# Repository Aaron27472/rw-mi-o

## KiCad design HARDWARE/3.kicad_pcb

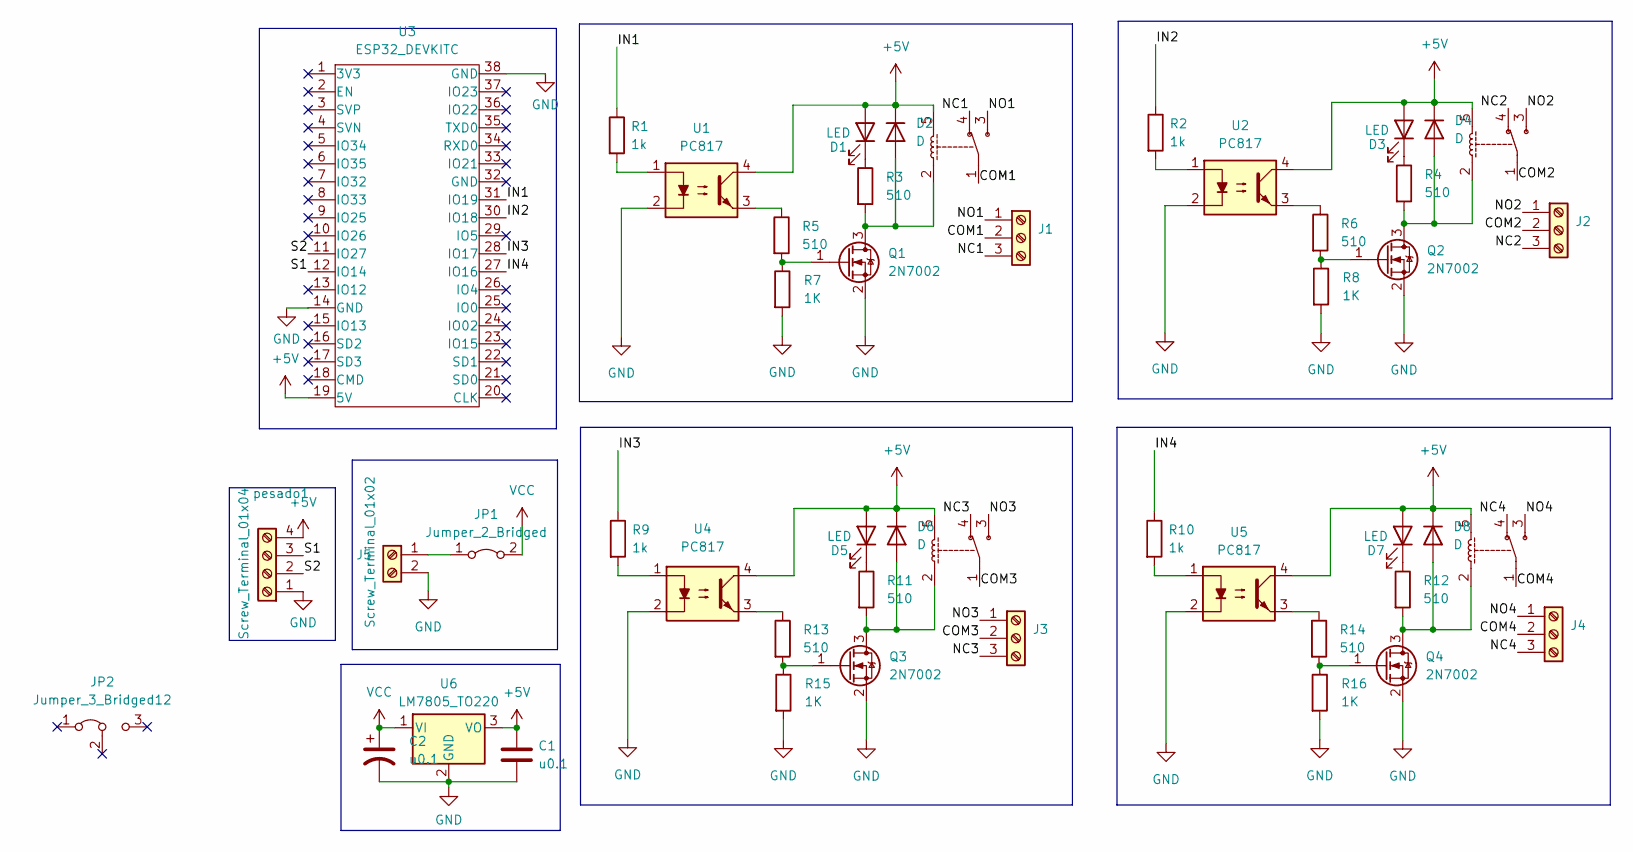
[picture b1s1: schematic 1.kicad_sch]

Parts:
C1, C2: u0.1; C_0805_2012Metric
D1, D3, D5, D7: LED; LED_0805_2012Metric
D2, D4, D6, D8: D; D_0805_2012Metric
J1, J2, J3, J4: Screw_Terminal_01x03; BORNERA3_AZUL
J5: Screw_Terminal_01x02; BORNERA2_AZUL
JP1: Jumper_2_Bridged; SolderJumper-2_P1.3mm_Bridged2Bar_Pad1.0x1.5mm
JP2: Jumper_3_Bridged12; alaisonmi
K1, K2, K3, K4: RELAY_C; Relay_C
Q1, Q2, Q3, Q4: 2N7002; SOT-23
R1, R2, R9, R10: 1k; R_0805_2012Metric
R3, R4, R5, R6, R11, R12, R13, R14: 510; R_0805_2012Metric
R7, R8, R15, R16: 1K; R_0805_2012Metric
U1, U2, U4, U5: PC817; DIP-4_PC817
U3: ESP32_DEVKITC
U6: LM7805_TO220; TO-263-2
pesado1: Screw_Terminal_01x04; PinHeader_1x04_P2.54mm_Vertical

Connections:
+5V: C1.1, D1.2 (A), D2.1 (K), D3.2 (A), D4.1 (K), D5.2 (A), D6.1 (K), D7.2 (A), D8.1 (K), K1.5, K2.5, K3.5, K4.5, U1.4, U2.4, U3.19 (5V), U4.4, U5.4, U6.3 (VO), pesado1.4
/COM1: J1.2, K1.1
/COM2: J2.2, K2.1
/COM3: J3.2, K3.1
/COM4: J4.2, K4.1
/IN1: R1.1, U3.31 (IO19)
/IN2: R2.1, U3.30 (IO18)
/IN3: R9.1, U3.28 (IO17)
/IN4: R10.1, U3.27 (IO16)
/NC1: J1.3, K1.4
/NC2: J2.3, K2.4
/NC3: J3.3, K3.4
/NC4: J4.3, K4.4
/NO1: J1.1, K1.3
/NO2: J2.1, K2.3
/NO3: J3.1, K3.3
/NO4: J4.1, K4.3
/S1: U3.12 (IO14), pesado1.3
/S2: U3.11 (IO27), pesado1.2
GND: C1.2, C2.2, J5.2, Q1.2 (S), Q2.2 (S), Q3.2 (S), Q4.2 (S), R7.2, R8.2, R15.2, R16.2, U1.2, U2.2, U3.14 (GND), U3.38 (GND), U4.2, U5.2, U6.2 (GND), pesado1.1
unnamed: D1.1 (K), R3.1
unnamed: D2.2 (A), K1.2, Q1.3 (D), R3.2
unnamed: D3.1 (K), R4.1
unnamed: D4.2 (A), K2.2, Q2.3 (D), R4.2
unnamed: D5.1 (K), R11.1
unnamed: D6.2 (A), K3.2, Q3.3 (D), R11.2
unnamed: D7.1 (K), R12.1
unnamed: D8.2 (A), K4.2, Q4.3 (D), R12.2
unnamed: J5.1, JP1.1 (A)
unnamed: Q1.1 (G), R5.2, R7.1
unnamed: Q2.1 (G), R6.2, R8.1
unnamed: Q3.1 (G), R13.2, R15.1
unnamed: Q4.1 (G), R14.2, R16.1
unnamed: R1.2, U1.1
unnamed: R2.2, U2.1
unnamed: R5.1, U1.3
unnamed: R6.1, U2.3
unnamed: R9.2, U4.1
unnamed: R10.2, U5.1
unnamed: R13.1, U4.3
unnamed: R14.1, U5.3
VCC: C2.1, JP1.2 (B), U6.1 (VI)

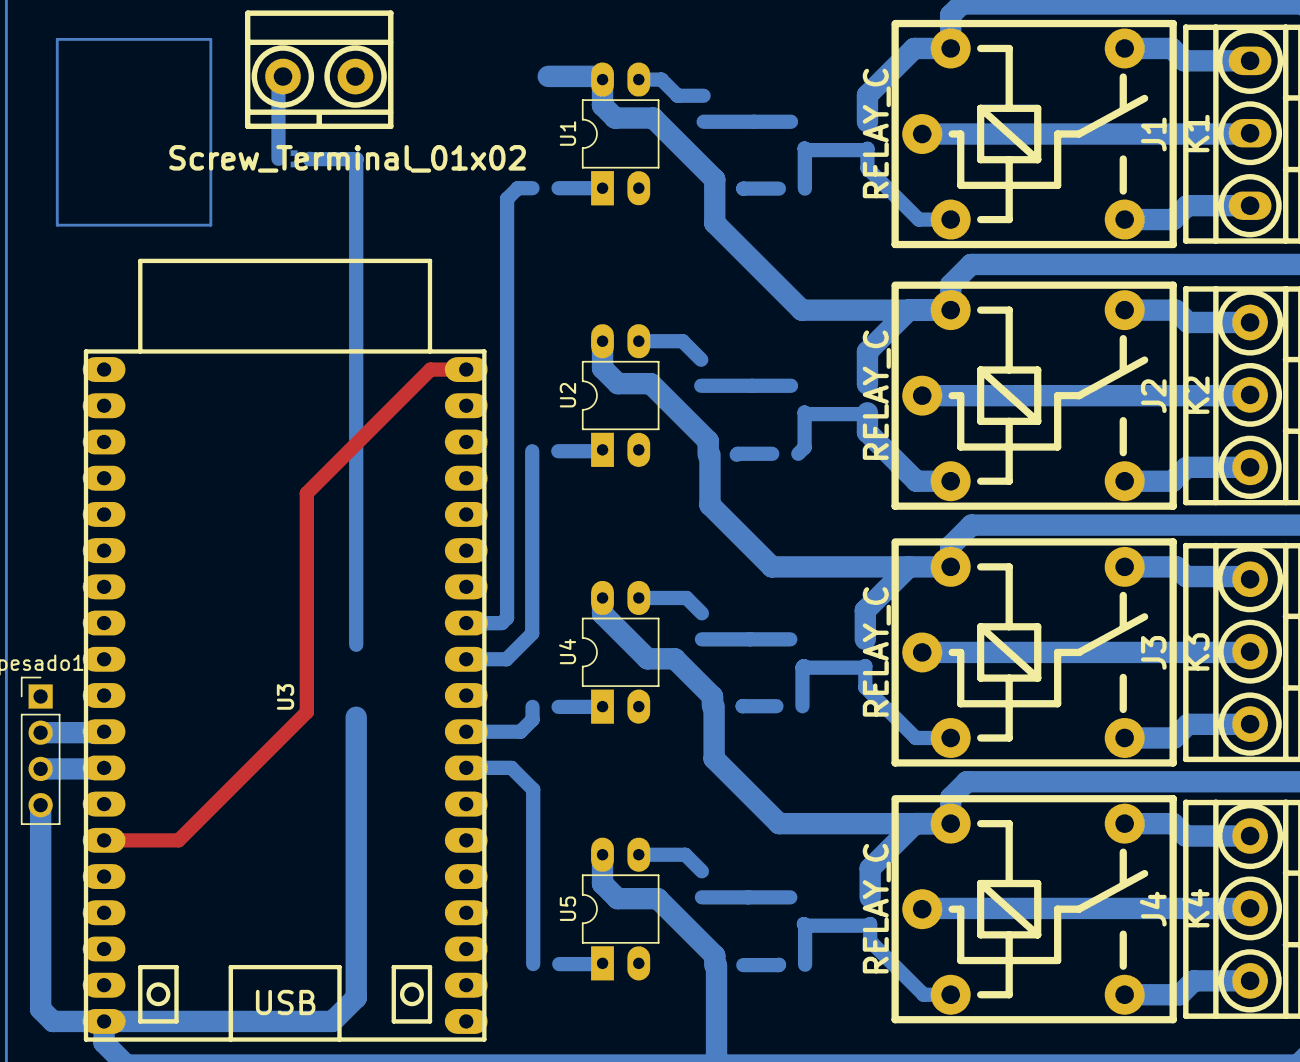
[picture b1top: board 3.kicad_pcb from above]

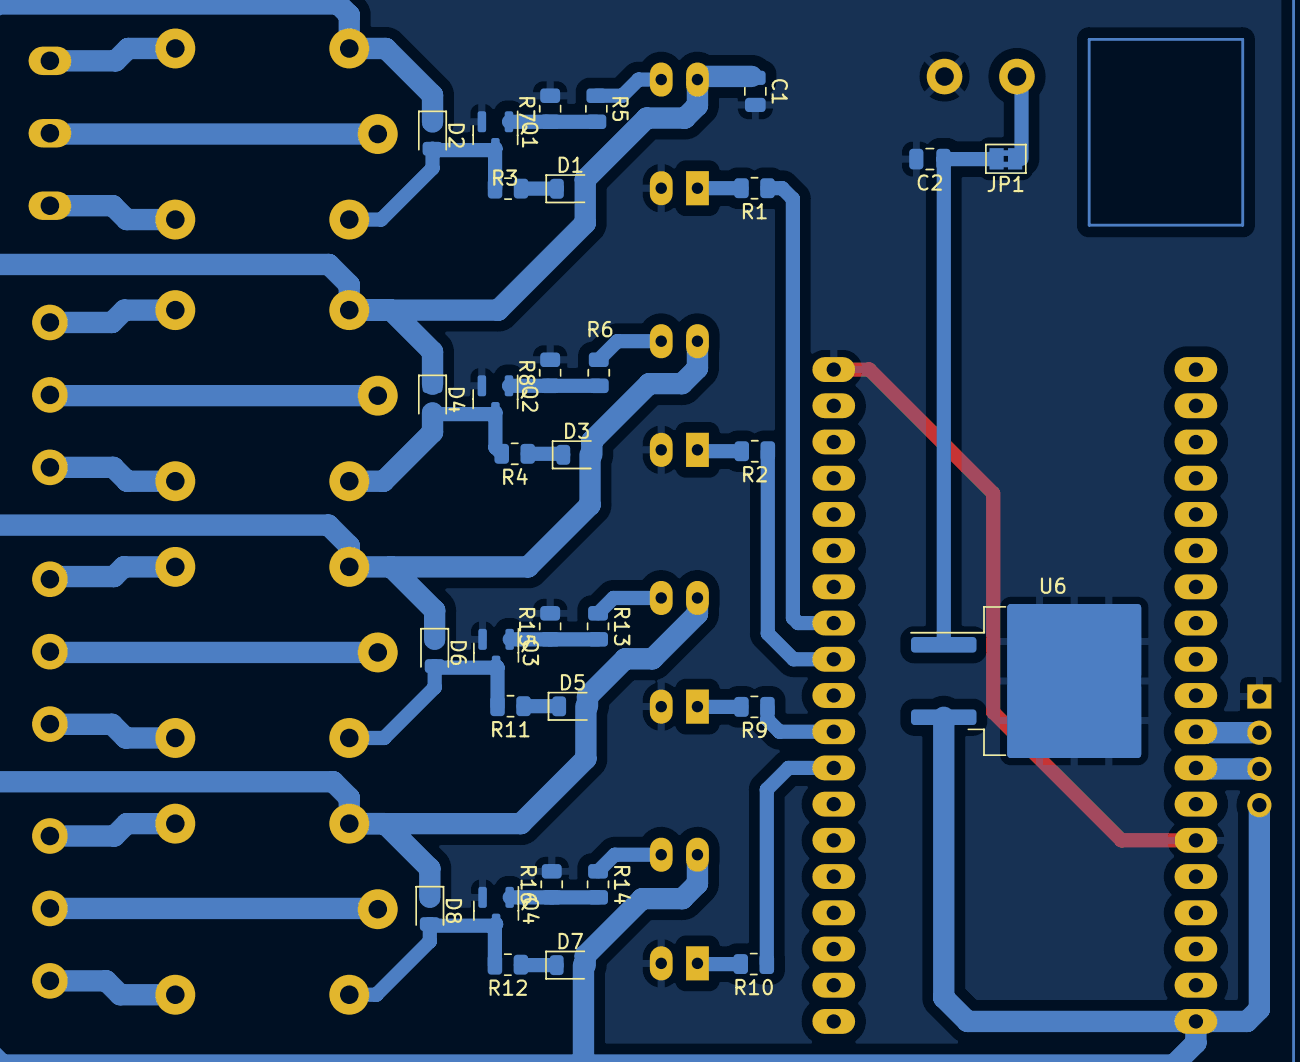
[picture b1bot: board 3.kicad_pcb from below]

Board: 2 copper layers, 48 parts (32 on the bottom side), 42 nets.

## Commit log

2025-06-17 relewifimiño
2025-06-18 relewifi
2025-06-19 modificacion1
2025-06-19 delet
2025-11-27 modificado
2025-11-27 modificando
2025-11-27 cambios
